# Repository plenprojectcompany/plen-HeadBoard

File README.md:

PLEN2 HeadBoard | PLEN Project Company
================================================================================

## Copyright (c) 2015,
- [Naohiro HAYAISHI](http://earlystone.com/)
- [PLEN Project Company Inc.](https://plen.jp)

## Build Environment
- Windows 8.1
- Eagle 6.60

## License
This material is released under the Creative Commons BY 4.0.

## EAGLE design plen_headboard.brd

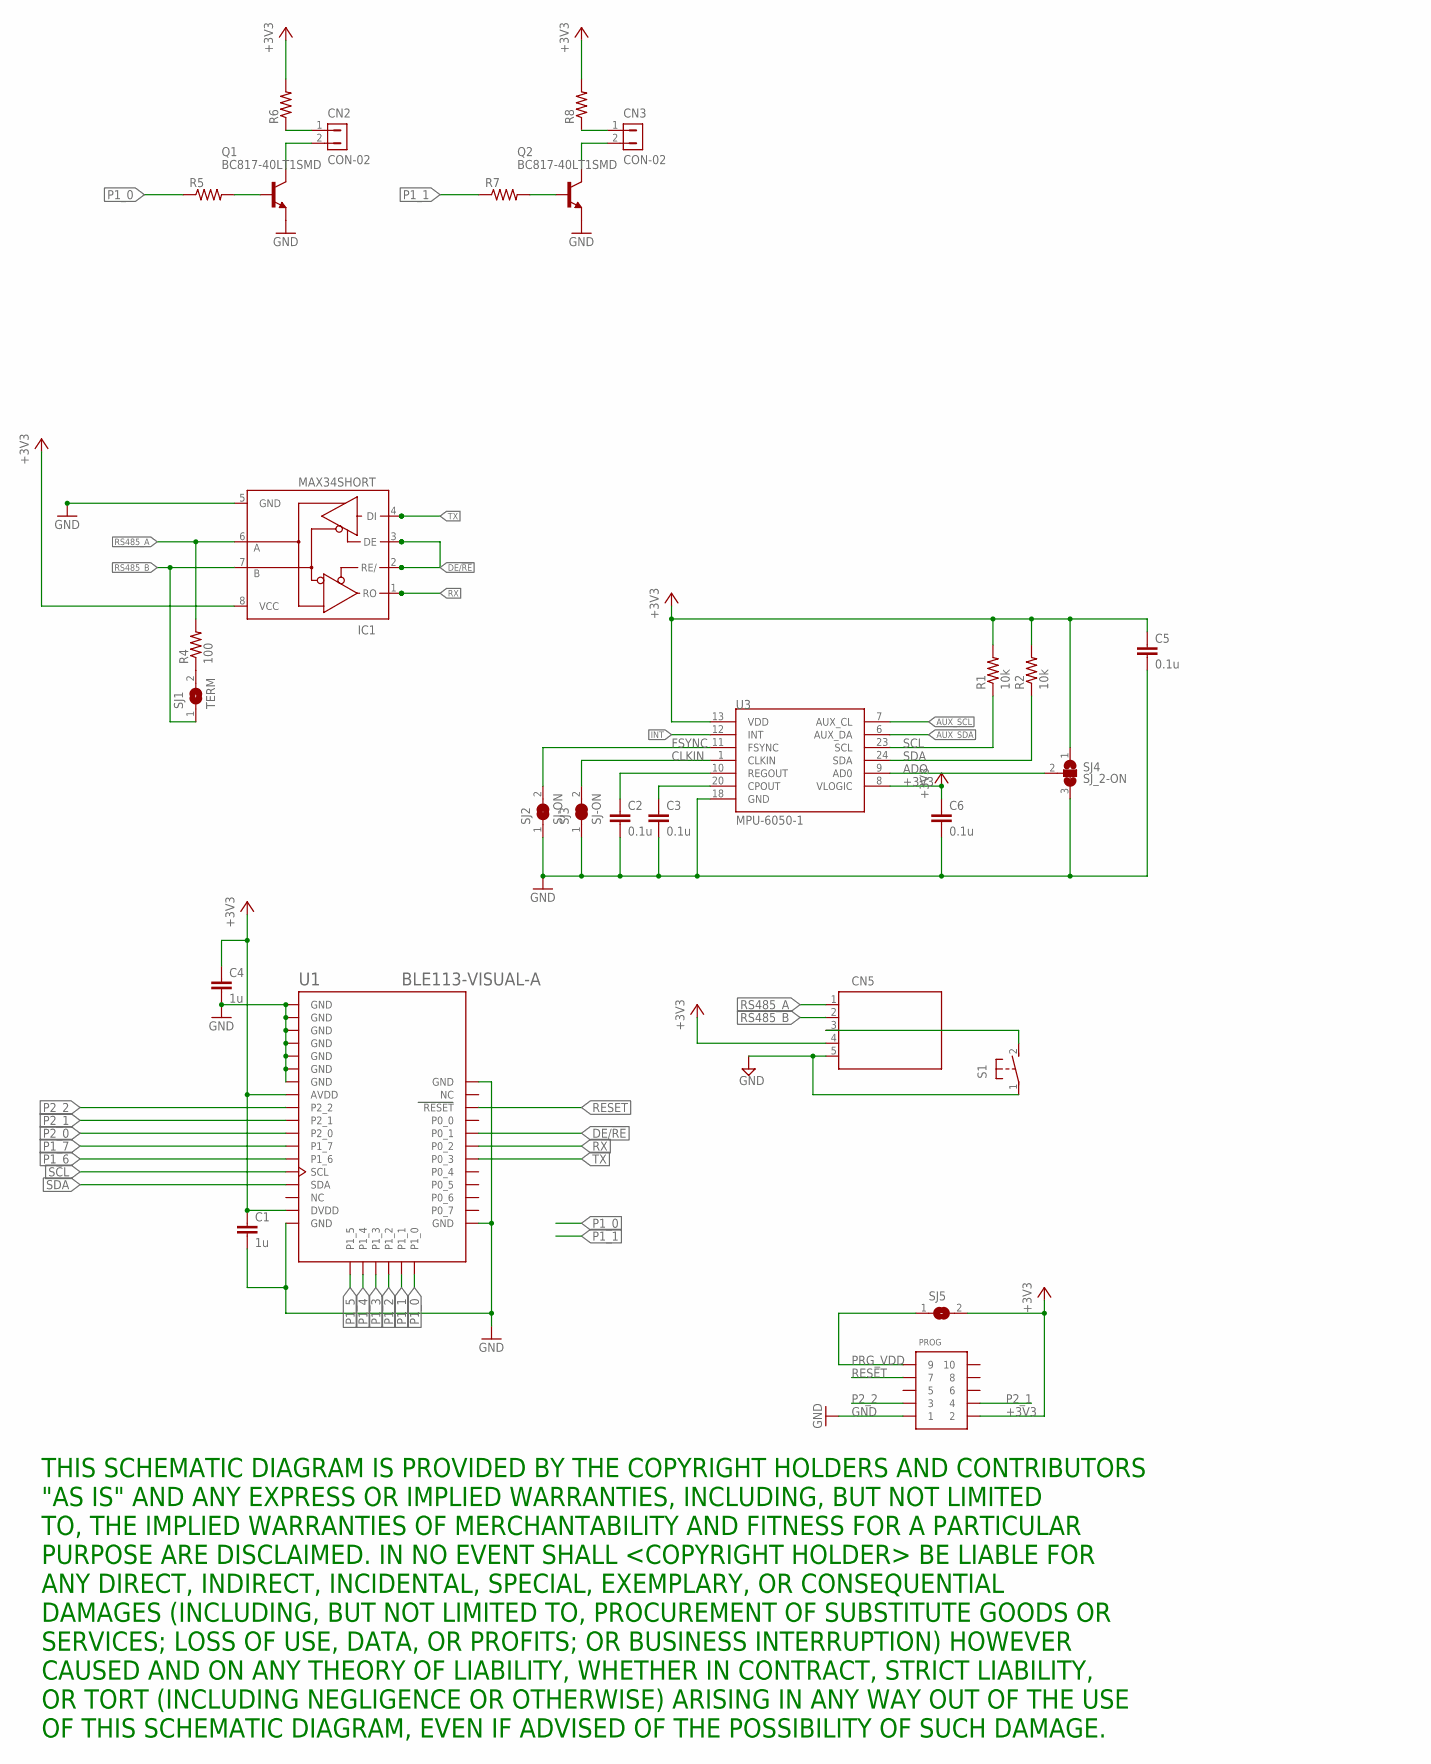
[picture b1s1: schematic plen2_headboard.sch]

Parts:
C1, C4: 1u; C0603
C2, C3, C5, C6: 0.1u; C0603
CN2, CN3: CON-02; SIP-100-02
CN5: 5PINZH; ZH-5
IC1: MAX34SHORT; SO08SHORT
PROG: CONN_5-2-FTSH-V; FTSH-105-DV
Q1, Q2: BC817-40LT1SMD; SOT23-BEC
R1, R2: 10k; R0603
R4: 100; R0603
R5, R6, R7, R8: R-US_R0603; R0603
S1: 31-XX; B3F-31XX
SJ1: TERM; SJ
SJ2, SJ3: SJ-ON
SJ4: SJ_2-ON
SJ5: SJ
U1: BLE113-VISUAL-A; BLE113-A
U3: MPU-6050-1; QFN-24-4MM2

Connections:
+3V3: C1.1, C4.1, C5.1, C6.1, CN5.4, IC1.8 (VCC), PROG.2, R1.2, R2.2, R6.2, R8.2, SJ4.1, SJ5.2, U1.AVDD, U1.DVDD, U3.8 (VLOGIC), U3.13 (VDD)
ADO: SJ4.2, U3.9 (AD0)
AUX_SCL: U3.7 (AUX_CL)
AUX_SDA: U3.6 (AUX_DA)
CLKIN: SJ3.2, U3.1 (CLKIN)
DE/!RE: IC1.2 (RE/), IC1.3 (DE), U1.P0_1
FSYNC: SJ2.2, U3.11 (FSYNC)
GND: C1.2, C2.2, C3.2, C4.2, C5.2, C6.2, CN5.5, IC1.5 (GND), PROG.1, Q1.E, Q2.E, S1.1, SJ2.1, SJ3.1, SJ4.3, U1.GND, U1.GND@2 (GND), U1.GND@3 (GND), U1.GND@4 (GND), U1.GND@5 (GND), U1.GND@6 (GND), U1.GND@7 (GND), U1.GND@8 (GND), U1.GND@9 (GND), U1.GND@10 (GND), U3.18 (GND)
INT: U3.12 (INT)
unnamed: C3.1, U3.20 (CPOUT)
unnamed: C2.1, U3.10 (REGOUT)
unnamed: R4.1, SJ1.2
unnamed: Q1.B, R5.2
unnamed: CN2.2, Q1.C
unnamed: CN2.1, R6.1
unnamed: Q2.B, R7.2
unnamed: CN3.2, Q2.C
unnamed: CN3.1, R8.1
unnamed: CN5.3, S1.2 (S)
P1_0: R5.1, U1.P1_0
P1_1: R7.1, U1.P1_1
P1_2: U1.P1_2
P1_3: U1.P1_3
P1_4: U1.P1_4
P1_5: U1.P1_5
P1_6: U1.P1_6
P1_7: U1.P1_7
P2_0: U1.P2_0
P2_1: PROG.4, U1.P2_1
P2_2: PROG.3, U1.P2_2
PRG_VDD: PROG.9, SJ5.1
RESET: PROG.7, U1.RESET
RS485_A: CN5.1, IC1.6 (A), R4.2
RS485_B: CN5.2, IC1.7 (B), SJ1.1
RX: IC1.1 (RO), U1.P0_2
SCL: R1.1, U1.SCL, U3.23 (SCL)
SDA: R2.1, U1.SDA, U3.24 (SDA)
TX: IC1.4 (DI), U1.P0_3

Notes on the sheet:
THIS SCHEMATIC DIAGRAM IS PROVIDED BY THE COPYRIGHT HOLDERS AND CONTRIBUTORS "AS IS" AND ANY EXPRESS OR IMPLIED WARRANTIES, INCLUDING, BUT NOT LIMITED TO, THE IMPLIED WARRANTIES OF MERCHANTABILITY AND FITNESS FOR A PARTICULAR PURPOSE ARE DISCLAIMED. IN NO EVENT SHALL <COPYRIGHT HOLDER> BE LIABLE FO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

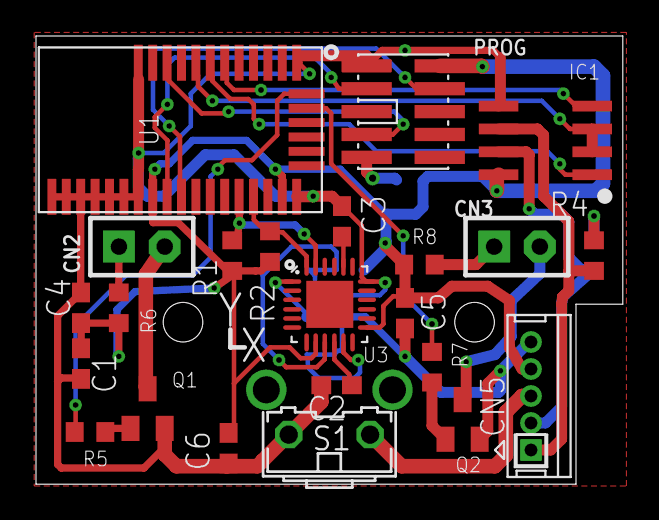
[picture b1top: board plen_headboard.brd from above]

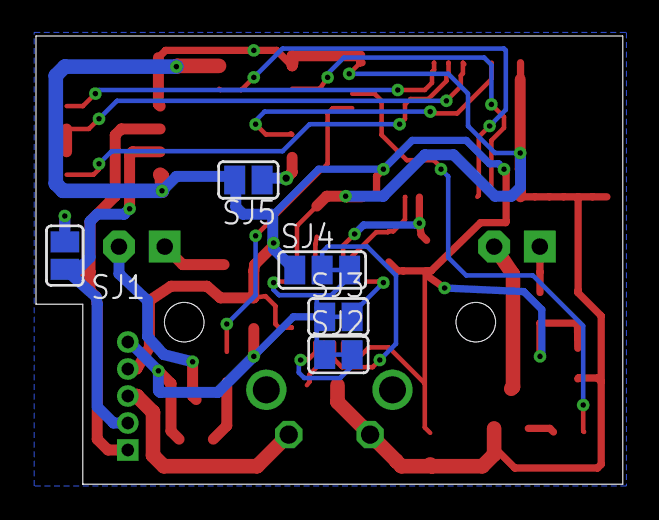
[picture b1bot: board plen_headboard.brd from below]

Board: 2 copper layers, 32.6 x 24.9 mm, 28 parts (5 on the bottom side), 28 nets.

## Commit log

2015-08-30 Added Eagle files.
2015-08-31 Fix LICENSE.md.
2016-04-14 Fix file-names & documents

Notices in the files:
parts and their libraries:
con-headers-jp: Copyright (C) 2004, Bob Starr (rtzaudio@mindspring.com)
